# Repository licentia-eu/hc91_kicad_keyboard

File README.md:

# HC 91, 40 Keys Cherry MX PCB

PCB for 40 Keys Cherry MX for HC 91/90/85

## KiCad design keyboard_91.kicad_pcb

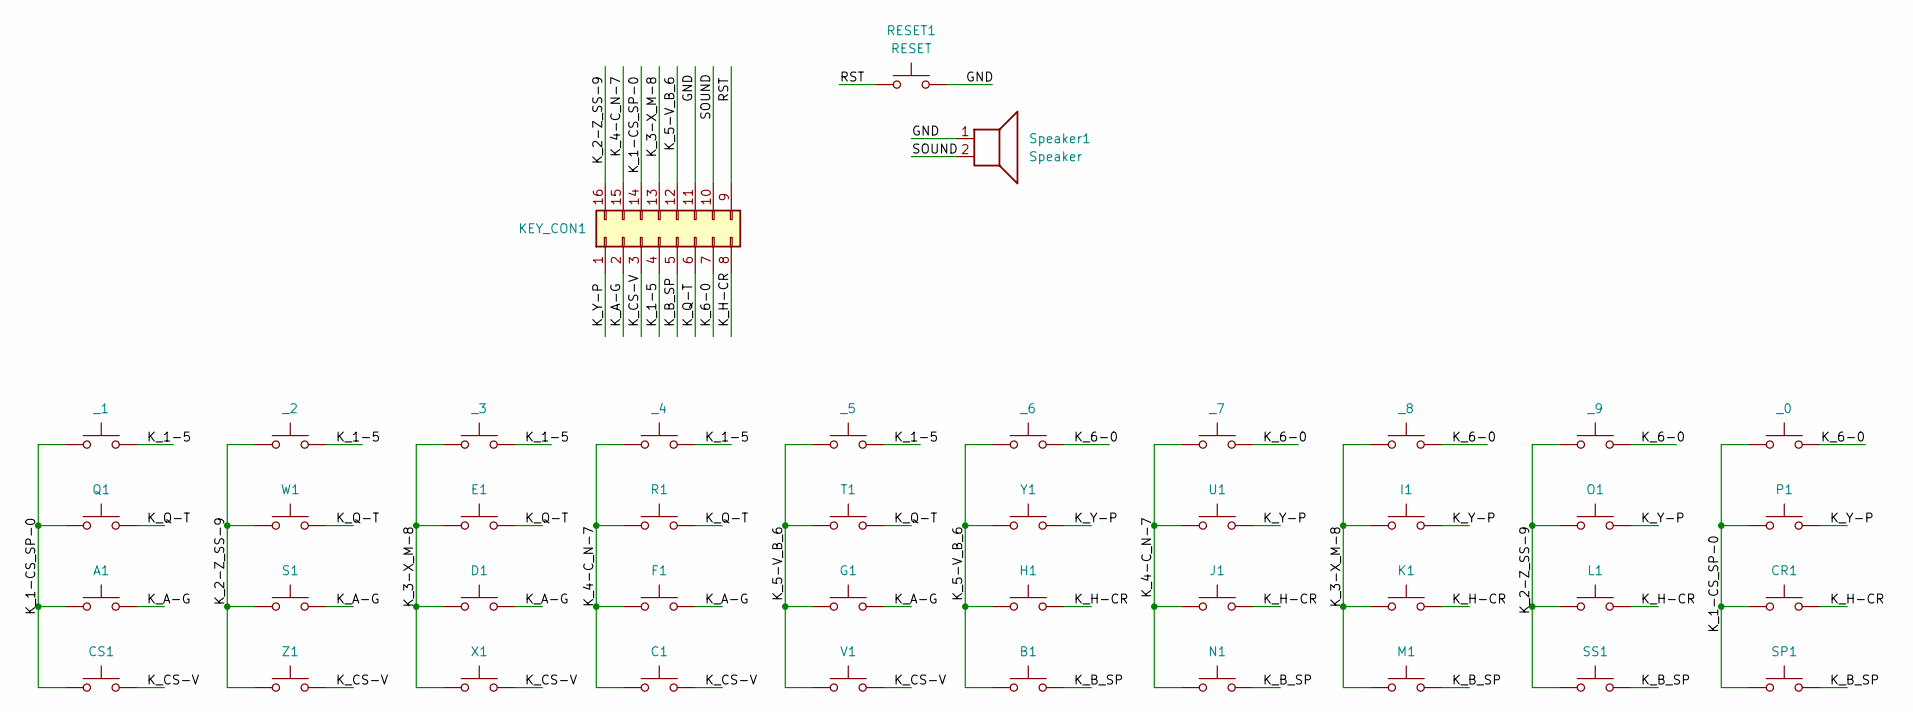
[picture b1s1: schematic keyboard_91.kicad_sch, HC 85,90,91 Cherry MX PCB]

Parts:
A1: SW_Cherry_MX_0.80u_Plate
B1: SW_Cherry_MX_0.80u_Plate
C1: SW_Cherry_MX_0.80u_Plate
CR1: SW_Cherry_MX_0.80u_Plate
CS1: SW_Cherry_MX_0.80u_Plate
D1: SW_Cherry_MX_0.80u_Plate
E1: SW_Cherry_MX_0.80u_Plate
F1: SW_Cherry_MX_0.80u_Plate
G1: SW_Cherry_MX_0.80u_Plate
H1: SW_Cherry_MX_0.80u_Plate
I1: SW_Cherry_MX_0.80u_Plate
J1: SW_Cherry_MX_0.80u_Plate
K1: SW_Cherry_MX_0.80u_Plate
KEY_CON1: Conn_02x08_Counter_Clockwise; DIP-16_276
L1: SW_Cherry_MX_0.80u_Plate
M1: SW_Cherry_MX_0.80u_Plate
N1: SW_Cherry_MX_0.80u_Plate
O1: SW_Cherry_MX_0.80u_Plate
P1: SW_Cherry_MX_0.80u_Plate
Q1: SW_Cherry_MX_0.80u_Plate
R1: SW_Cherry_MX_0.80u_Plate
RESET1: RESET; SIP-2
S1: SW_Cherry_MX_0.80u_Plate
SP1: SW_Cherry_MX_0.80u_Plate
SS1: SW_Cherry_MX_0.80u_Plate
Speaker1: Speaker; SIP-2
T1: SW_Cherry_MX_0.80u_Plate
U1: SW_Cherry_MX_0.80u_Plate
V1: SW_Cherry_MX_0.80u_Plate
W1: SW_Cherry_MX_0.80u_Plate
X1: SW_Cherry_MX_0.80u_Plate
Y1: SW_Cherry_MX_0.80u_Plate
Z1: SW_Cherry_MX_0.80u_Plate
_0, _1, _2, _3, _4, _5, _6, _7, _8, _9: SW_Cherry_MX_0.80u_Plate

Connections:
/GND: KEY_CON1.11, RESET1.2, Speaker1.1
/K_1-5: KEY_CON1.4, _1.2, _2.2, _3.2, _4.2, _5.2
/K_1-CS_SP-0: A1.1, CR1.1, CS1.1, KEY_CON1.14, P1.1, Q1.1, SP1.1, _0.1, _1.1
/K_2-Z_SS-9: KEY_CON1.16, L1.1, O1.1, S1.1, SS1.1, W1.1, Z1.1, _2.1, _9.1
/K_3-X_M-8: D1.1, E1.1, I1.1, K1.1, KEY_CON1.13, M1.1, X1.1, _3.1, _8.1
/K_4-C_N-7: C1.1, F1.1, J1.1, KEY_CON1.15, N1.1, R1.1, U1.1, _4.1, _7.1
/K_5-V_B_6: B1.1, G1.1, H1.1, KEY_CON1.12, T1.1, V1.1, Y1.1, _5.1, _6.1
/K_6-0: KEY_CON1.7, _0.2, _6.2, _7.2, _8.2, _9.2
/K_A-G: A1.2, D1.2, F1.2, G1.2, KEY_CON1.2, S1.2
/K_B_SP: B1.2, KEY_CON1.5, M1.2, N1.2, SP1.2, SS1.2
/K_CS-V: C1.2, CS1.2, KEY_CON1.3, V1.2, X1.2, Z1.2
/K_H-CR: CR1.2, H1.2, J1.2, K1.2, KEY_CON1.8, L1.2
/K_Q-T: E1.2, KEY_CON1.6, Q1.2, R1.2, T1.2, W1.2
/K_Y-P: I1.2, KEY_CON1.1, O1.2, P1.2, U1.2, Y1.2
/RST: KEY_CON1.9, RESET1.1
/SOUND: KEY_CON1.10, Speaker1.2

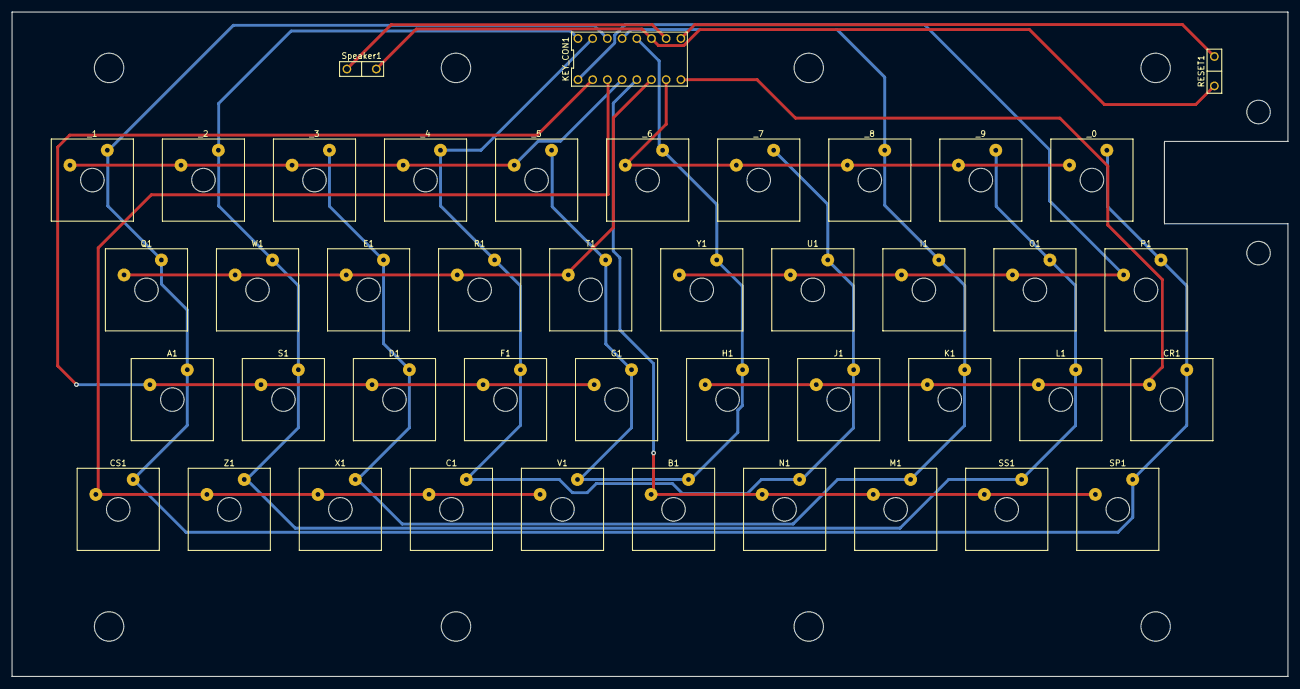
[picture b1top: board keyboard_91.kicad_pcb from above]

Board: 2 copper layers, 217.0 x 113.0 mm, 43 parts (0 on the bottom side), 16 nets.

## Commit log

2022-04-18 Say hello to HC91 40 Keys Cherry MX Keyboard
2022-04-19 Moure touches
    - hide useless stuff
    - add reset buttons SIP
    - add speaker SIP
2022-05-23 Second try
    - fixed cherry mx holes (make them 0.8 mm)
    - fixed connector holes
    - fixed sound & reset holes
